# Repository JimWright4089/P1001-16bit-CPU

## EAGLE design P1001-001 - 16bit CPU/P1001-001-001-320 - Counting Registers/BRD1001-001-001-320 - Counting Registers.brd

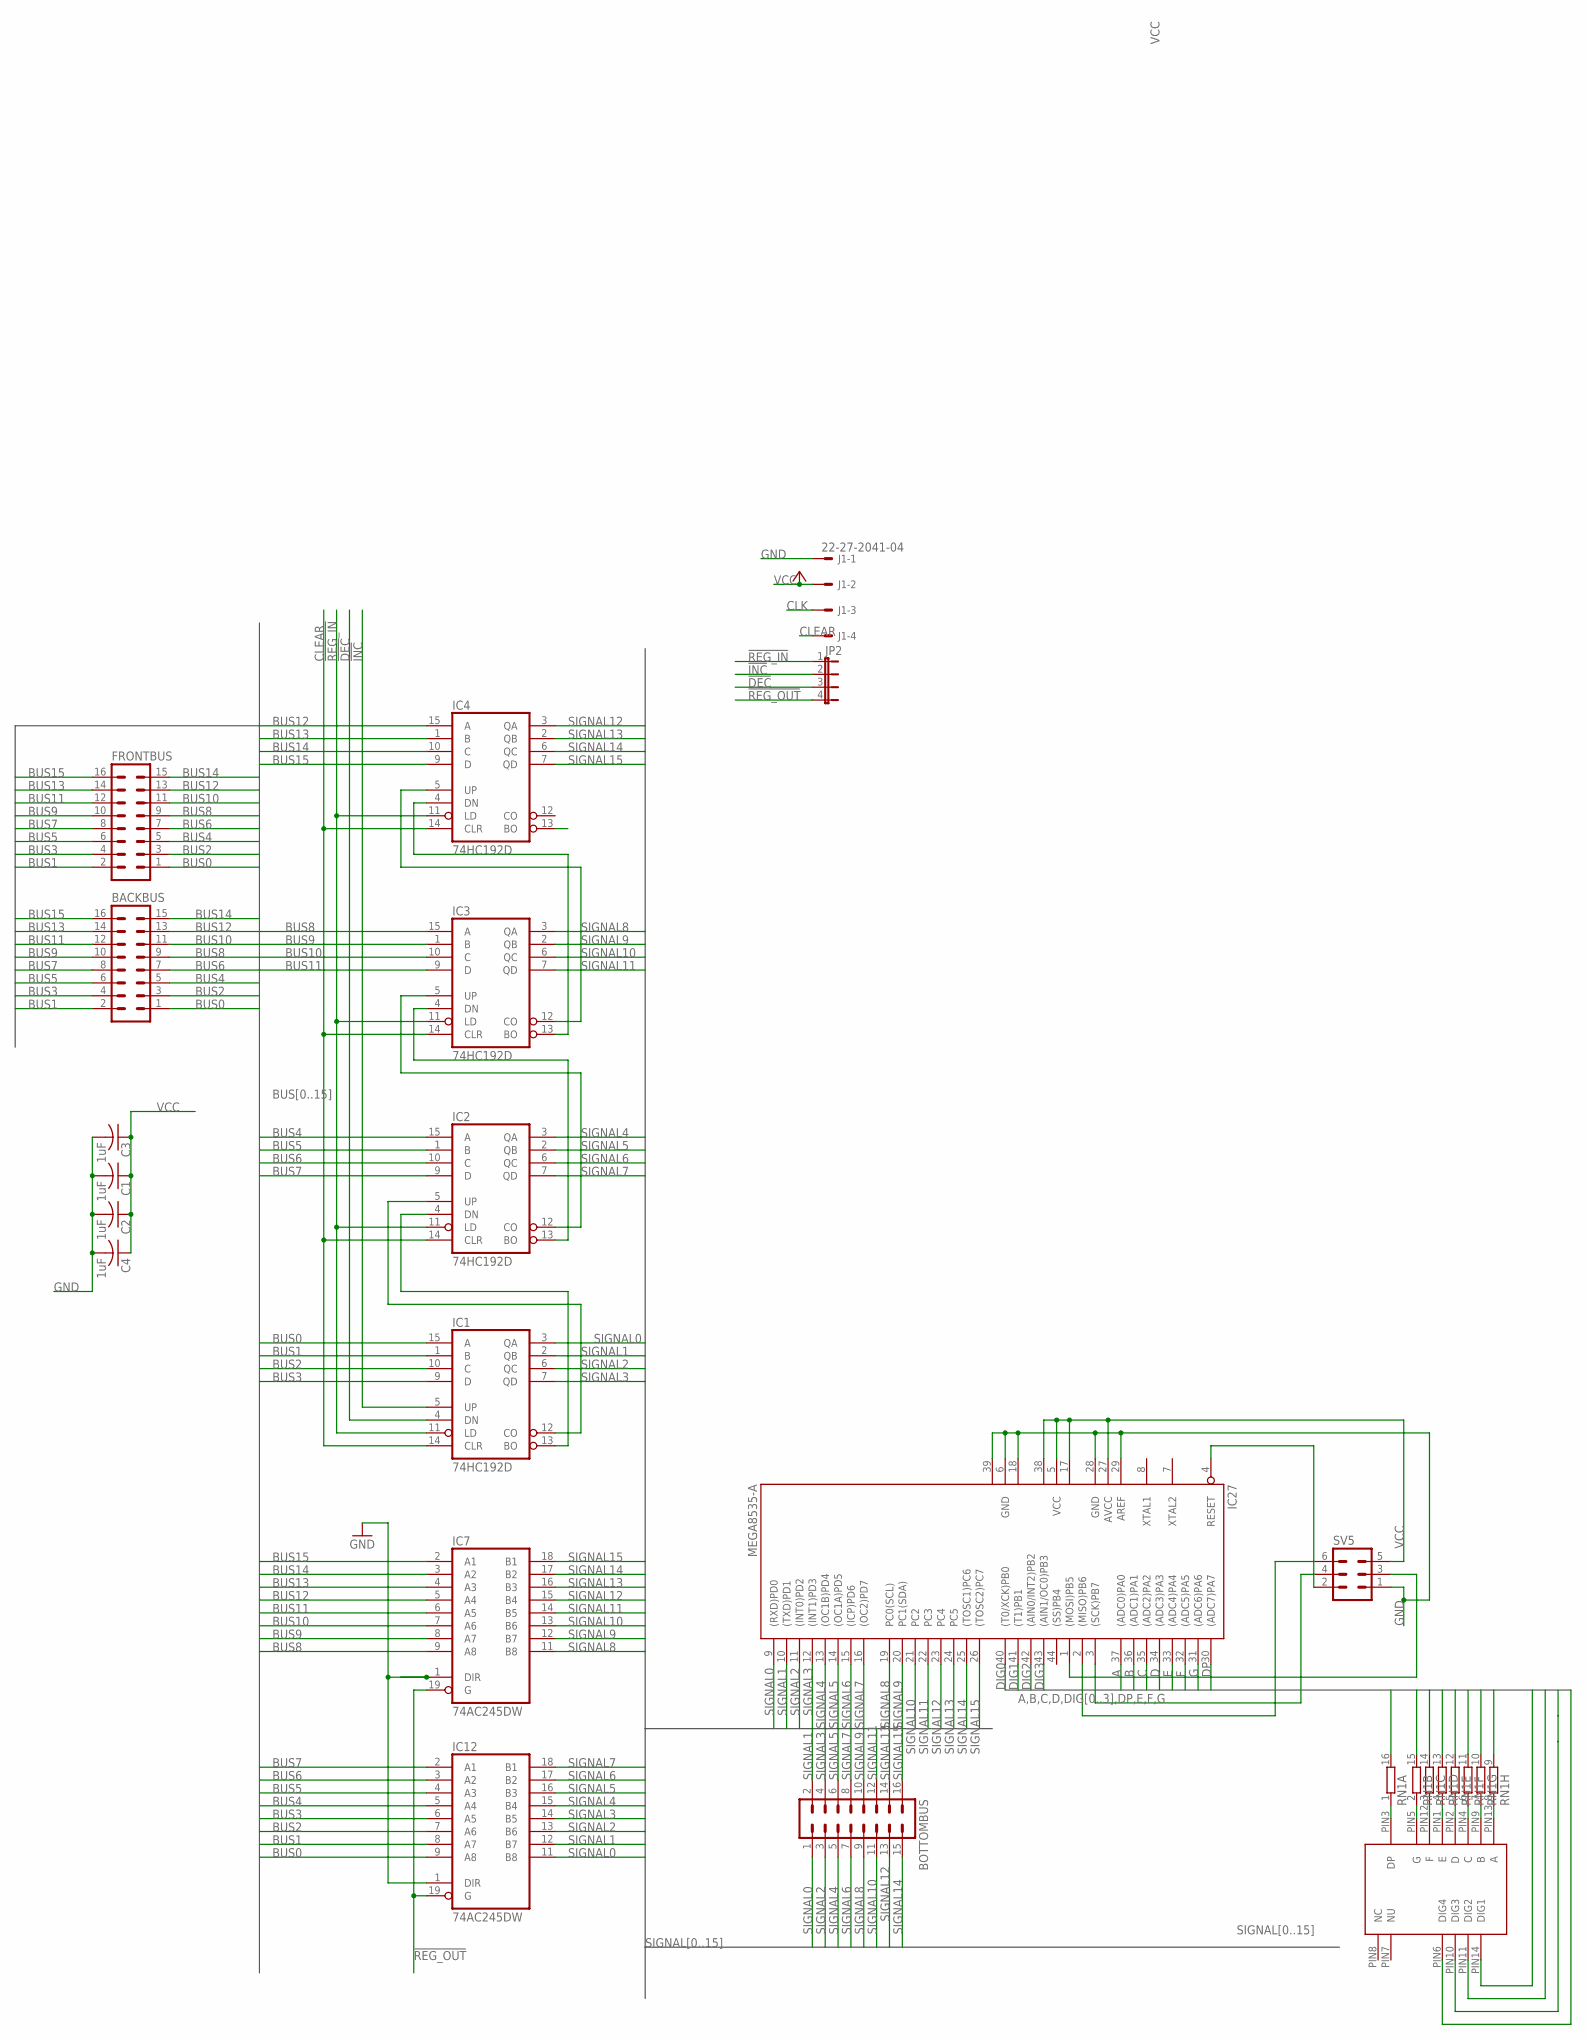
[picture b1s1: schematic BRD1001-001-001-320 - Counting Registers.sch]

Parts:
BACKBUS: ML16
BOTTOMBUS: ML16
C1, C2, C3, C4: 1uF; C1206
FRONTBUS: ML16
IC1, IC2, IC3, IC4: 74HC192D; SO16
IC7, IC12: 74AC245DW; SO20W
IC27: MEGA8535-A; TQFP44
J1: 22-27-2041-04; 6410-04
JP2: JP4E; JP4
RN1: 8R-NSOMC; SOMC16
SV5: ML6
U$1: 4-DIGIT-7-SEGMENT

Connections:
!DEC: IC1.4 (DN), JP2.3
!INC: IC1.5 (UP), JP2.2
!REG_IN: IC1.11 (LD), IC2.11 (LD), IC3.11 (LD), IC4.11 (LD), JP2.1
!REG_OUT: IC7.19 (G), IC12.19 (G), JP2.4
A: IC27.37 ((ADC0)PA0), RN1.9 (2)
B: IC27.36 ((ADC1)PA1), RN1.10 (2)
BUS0: BACKBUS.1, FRONTBUS.1, IC1.15 (A), IC12.9 (A8)
BUS1: BACKBUS.2, FRONTBUS.2, IC1.1 (B), IC12.8 (A7)
BUS2: BACKBUS.3, FRONTBUS.3, IC1.10 (C), IC12.7 (A6)
BUS3: BACKBUS.4, FRONTBUS.4, IC1.9 (D), IC12.6 (A5)
BUS4: BACKBUS.5, FRONTBUS.5, IC2.15 (A), IC12.5 (A4)
BUS5: BACKBUS.6, FRONTBUS.6, IC2.1 (B), IC12.4 (A3)
BUS6: BACKBUS.7, FRONTBUS.7, IC2.10 (C), IC12.3 (A2)
BUS7: BACKBUS.8, FRONTBUS.8, IC2.9 (D), IC12.2 (A1)
BUS8: BACKBUS.9, FRONTBUS.9, IC3.15 (A), IC7.9 (A8)
BUS9: BACKBUS.10, FRONTBUS.10, IC3.1 (B), IC7.8 (A7)
BUS10: BACKBUS.11, FRONTBUS.11, IC3.10 (C), IC7.7 (A6)
BUS11: BACKBUS.12, FRONTBUS.12, IC3.9 (D), IC7.6 (A5)
BUS12: BACKBUS.13, FRONTBUS.13, IC4.15 (A), IC7.5 (A4)
BUS13: BACKBUS.14, FRONTBUS.14, IC4.1 (B), IC7.4 (A3)
BUS14: BACKBUS.15, FRONTBUS.15, IC4.10 (C), IC7.3 (A2)
BUS15: BACKBUS.16, FRONTBUS.16, IC4.9 (D), IC7.2 (A1)
C: IC27.35 ((ADC2)PA2), RN1.11 (2)
CLEAR: IC1.14 (CLR), IC2.14 (CLR), IC3.14 (CLR), IC4.14 (CLR), J1.4
CLK: J1.3
D: IC27.34 ((ADC3)PA3), RN1.12 (2)
DIG0: IC27.40 ((T0/XCK)PB0), U$1.PIN14 (DIG1)
DIG1: IC27.41 ((T1)PB1), U$1.PIN11 (DIG2)
DIG2: IC27.42 ((AIN0/INT2)PB2), U$1.PIN10 (DIG3)
DIG3: IC27.43 ((AIN1/OC0)PB3), U$1.PIN6 (DIG4)
DP: IC27.30 ((ADC7)PA7), RN1.16 (2)
E: IC27.33 ((ADC4)PA4), RN1.13 (2)
F: IC27.32 ((ADC5)PA5), RN1.14 (2)
G: IC27.31 ((ADC6)PA6), RN1.15 (2)
GND: C1.2, C2.2, C3.2, C4.2, IC1.8 (GND), IC2.8 (GND), IC3.8 (GND), IC4.8 (GND), IC7.1 (DIR), IC7.10 (GND), IC12.1 (DIR), IC12.10 (GND), IC27.6 (GND), IC27.18 (GND1), IC27.28 (GND), IC27.29 (AREF), IC27.39 (GND2), J1.1, SV5.1
unnamed: IC1.12 (CO), IC2.5 (UP)
unnamed: IC1.13 (BO), IC2.4 (DN)
unnamed: IC2.12 (CO), IC3.5 (UP)
unnamed: IC2.13 (BO), IC3.4 (DN)
unnamed: IC3.12 (CO), IC4.5 (UP)
unnamed: IC3.13 (BO), IC4.4 (DN)
unnamed: IC27.1 ((MOSI)PB5), SV5.3
unnamed: IC27.3 ((SCK)PB7), SV5.4
unnamed: IC27.2 ((MISO)PB6), SV5.6
unnamed: IC27.4 (RESET), SV5.2
unnamed: RN1.8 (1), U$1.PIN13 (A)
unnamed: RN1.7 (1), U$1.PIN9 (B)
unnamed: RN1.6 (1), U$1.PIN4 (C)
unnamed: RN1.5 (1), U$1.PIN2 (D)
unnamed: RN1.4 (1), U$1.PIN1 (E)
unnamed: RN1.3 (1), U$1.PIN12 (F)
unnamed: RN1.2 (1), U$1.PIN5 (G)
unnamed: RN1.1, U$1.PIN3 (DP)
SIGNAL0: BOTTOMBUS.1, IC1.3 (QA), IC12.11 (B8), IC27.9 ((RXD)PD0)
SIGNAL1: BOTTOMBUS.2, IC1.2 (QB), IC12.12 (B7), IC27.10 ((TXD)PD1)
SIGNAL2: BOTTOMBUS.3, IC1.6 (QC), IC12.13 (B6), IC27.11 ((INT0)PD2)
SIGNAL3: BOTTOMBUS.4, IC1.7 (QD), IC12.14 (B5), IC27.12 ((INT1)PD3)
SIGNAL4: BOTTOMBUS.5, IC2.3 (QA), IC12.15 (B4), IC27.13 ((OC1B)PD4)
SIGNAL5: BOTTOMBUS.6, IC2.2 (QB), IC12.16 (B3), IC27.14 ((OC1A)PD5)
SIGNAL6: BOTTOMBUS.7, IC2.6 (QC), IC12.17 (B2), IC27.15 ((ICP)PD6)
SIGNAL7: BOTTOMBUS.8, IC2.7 (QD), IC12.18 (B1), IC27.16 ((OC2)PD7)
SIGNAL8: BOTTOMBUS.9, IC3.3 (QA), IC7.11 (B8), IC27.19 (PC0(SCL))
SIGNAL9: BOTTOMBUS.10, IC3.2 (QB), IC7.12 (B7), IC27.20 (PC1(SDA))
SIGNAL10: BOTTOMBUS.11, IC3.6 (QC), IC7.13 (B6), IC27.21 (PC2)
SIGNAL11: BOTTOMBUS.12, IC3.7 (QD), IC7.14 (B5), IC27.22 (PC3)
SIGNAL12: BOTTOMBUS.13, IC4.3 (QA), IC7.15 (B4), IC27.23 (PC4)
SIGNAL13: BOTTOMBUS.14, IC4.2 (QB), IC7.16 (B3), IC27.24 (PC5)
SIGNAL14: BOTTOMBUS.15, IC4.6 (QC), IC7.17 (B2), IC27.25 ((TOSC1)PC6)
SIGNAL15: BOTTOMBUS.16, IC4.7 (QD), IC7.18 (B1), IC27.26 ((TOSC2)PC7)
VCC: C1.1, C2.1, C3.1, C4.1, IC1.16 (VCC), IC2.16 (VCC), IC3.16 (VCC), IC4.16 (VCC), IC7.20 (VCC), IC12.20 (VCC), IC27.5 (VCC), IC27.17 (VCC1), IC27.27 (AVCC), IC27.38 (VCC2), J1.2, SV5.5

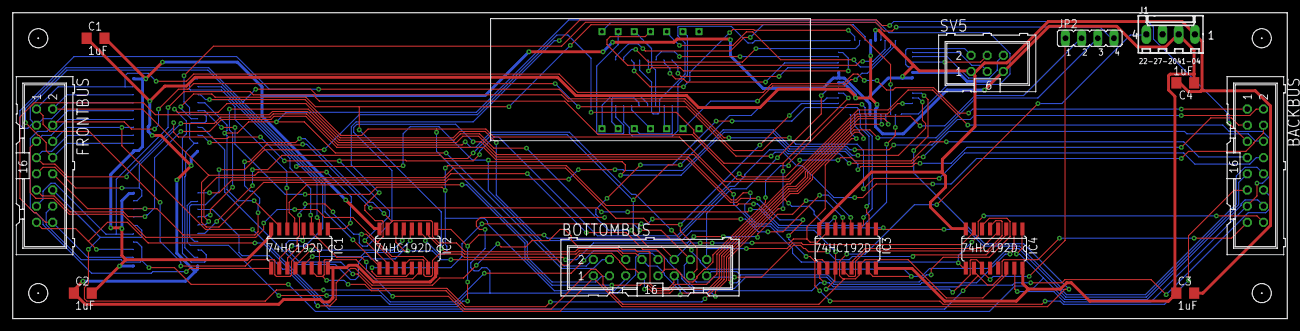
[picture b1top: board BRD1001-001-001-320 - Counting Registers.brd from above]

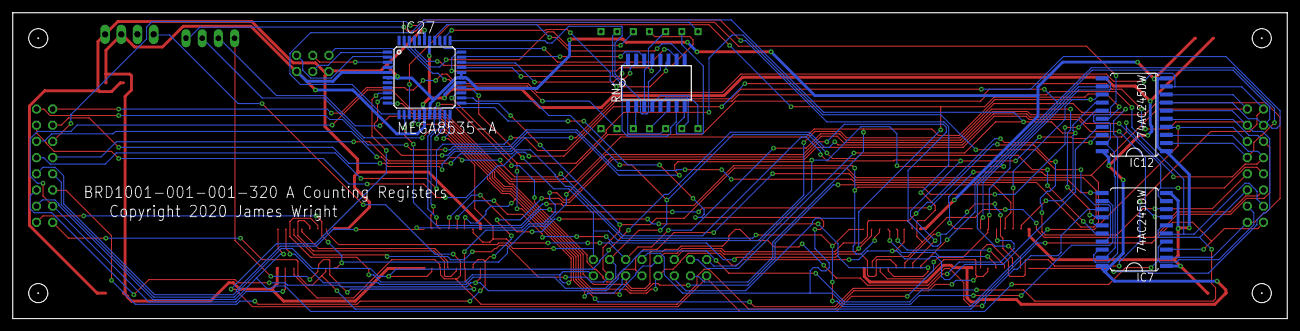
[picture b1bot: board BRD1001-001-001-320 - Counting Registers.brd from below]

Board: 2 copper layers, 200.0 x 48.0 mm, 19 parts (4 on the bottom side), 69 nets.

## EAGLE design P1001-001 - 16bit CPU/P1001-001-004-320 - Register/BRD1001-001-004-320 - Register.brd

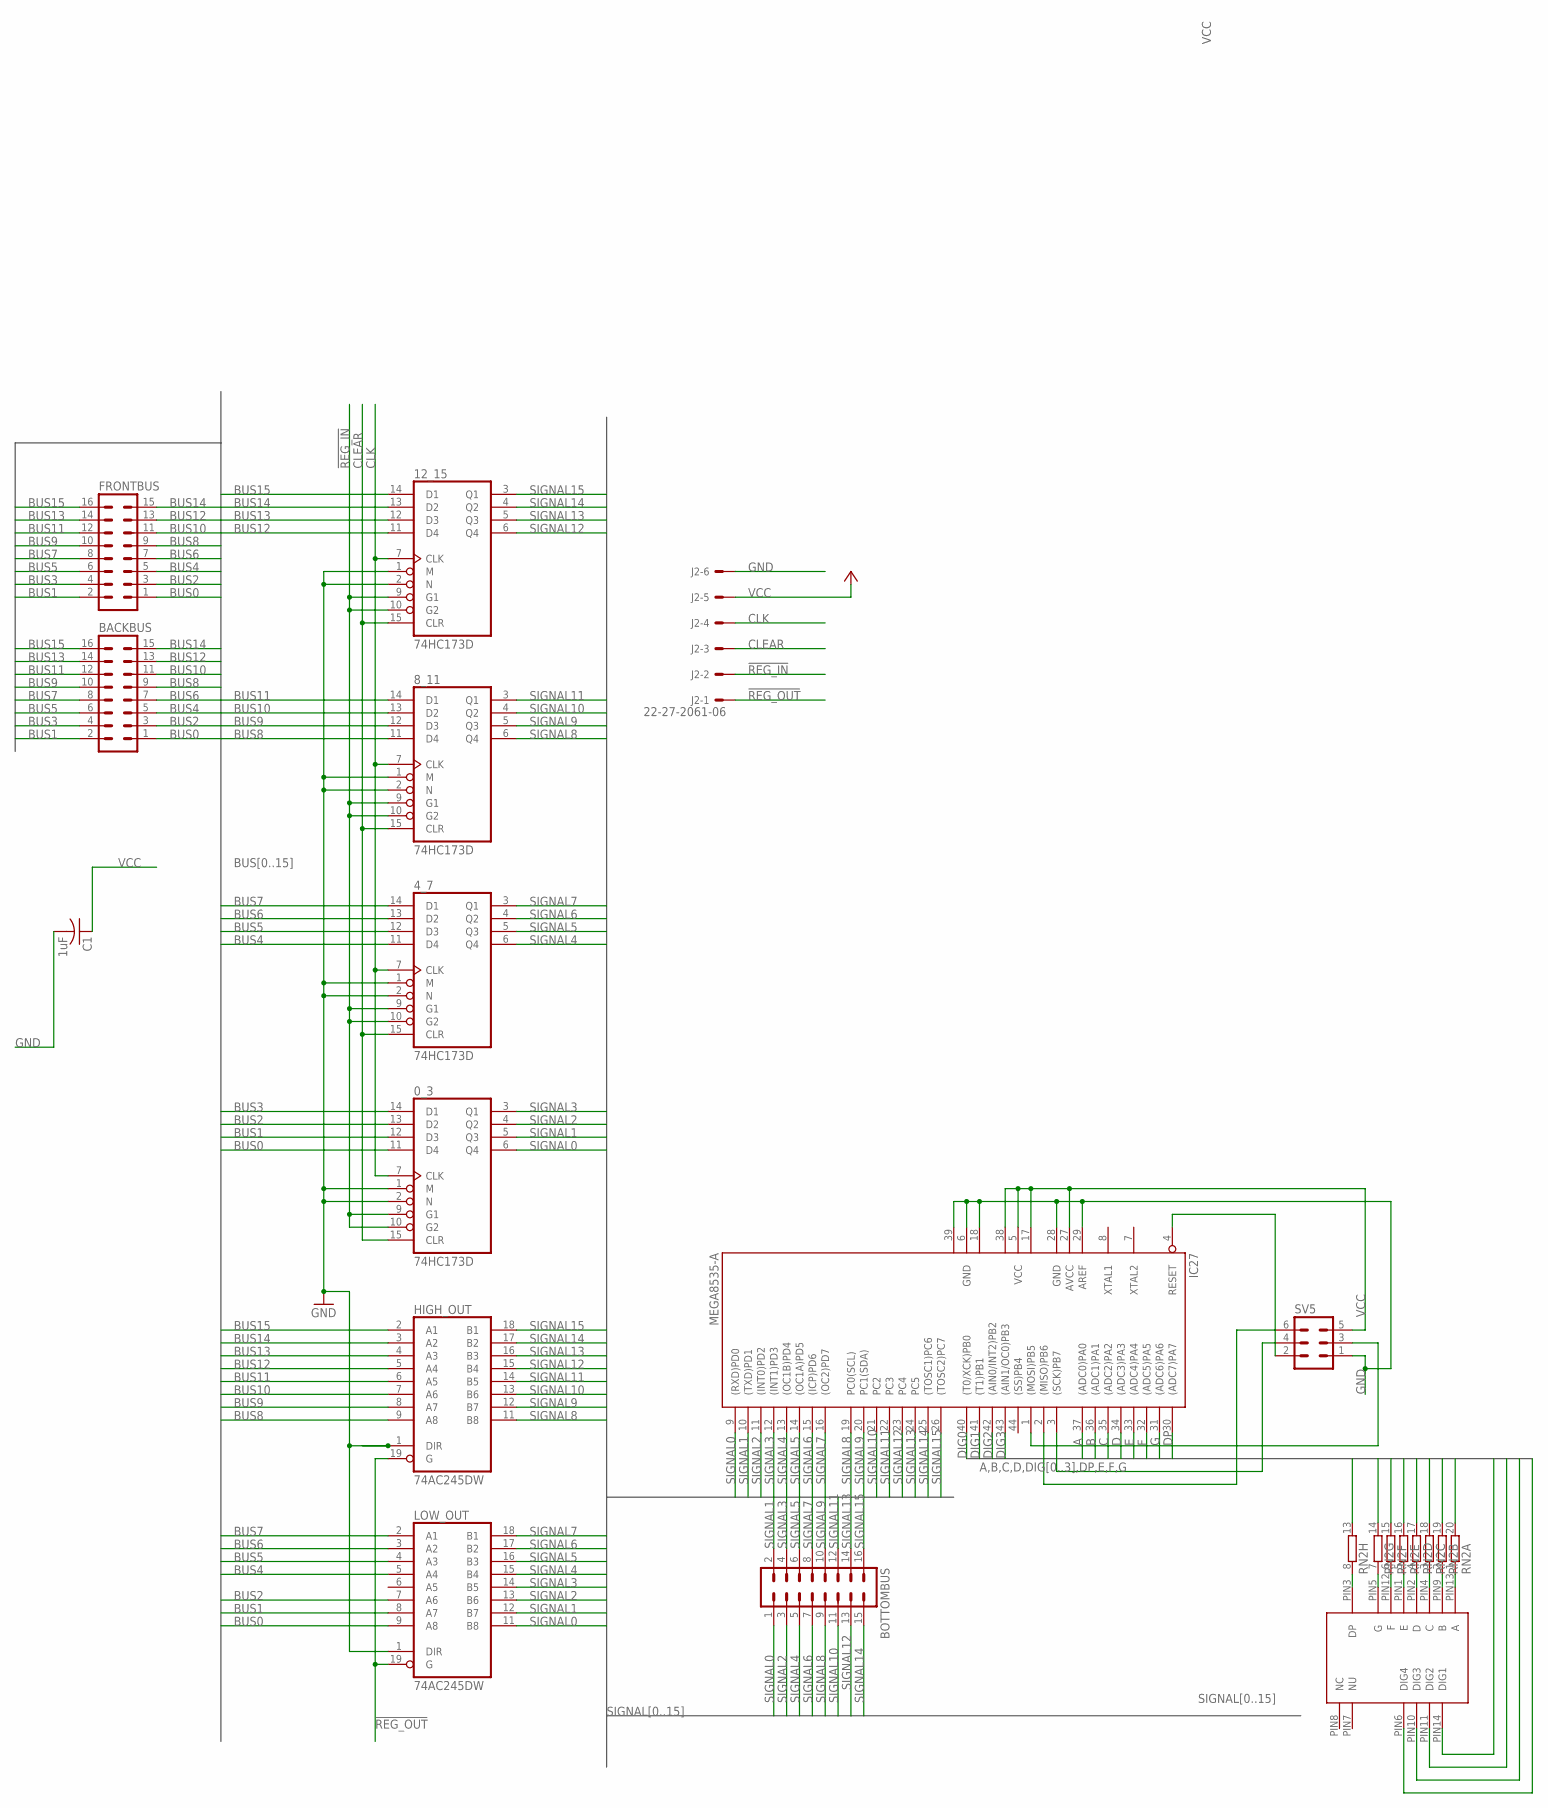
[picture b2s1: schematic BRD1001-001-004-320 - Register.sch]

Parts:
0_3, 4_7, 8_11, 12_15: 74HC173D; SO16
BACKBUS: ML16
BOTTOMBUS: ML16
C1: 1uF; C1206
FRONTBUS: ML16
HIGH_OUT: 74AC245DW; SO20W
IC27: MEGA8535-A; TQFP44
J2: 22-27-2061-06; 6410-06
LOW_OUT: 74AC245DW; SO20W
RN2: 10R-NSOMC; SOMC20
SV5: ML6
U$1: 4-DIGIT-7-SEGMENT

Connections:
!REG_IN: 0_3.9 (G1), 0_3.10 (G2), 4_7.9 (G1), 4_7.10 (G2), 8_11.9 (G1), 8_11.10 (G2), 12_15.9 (G1), 12_15.10 (G2), J2.2
!REG_OUT: HIGH_OUT.19 (G), J2.1, LOW_OUT.19 (G)
A: IC27.37 ((ADC0)PA0), RN2.20 (2)
B: IC27.36 ((ADC1)PA1), RN2.19 (2)
BUS0: 0_3.11 (D4), BACKBUS.1, FRONTBUS.1, LOW_OUT.9 (A8)
BUS1: 0_3.12 (D3), BACKBUS.2, FRONTBUS.2, LOW_OUT.8 (A7)
BUS2: 0_3.13 (D2), BACKBUS.3, FRONTBUS.3, LOW_OUT.7 (A6)
BUS3: 0_3.14 (D1), BACKBUS.4, FRONTBUS.4
BUS4: 4_7.11 (D4), BACKBUS.5, FRONTBUS.5, LOW_OUT.5 (A4)
BUS5: 4_7.12 (D3), BACKBUS.6, FRONTBUS.6, LOW_OUT.4 (A3)
BUS6: 4_7.13 (D2), BACKBUS.7, FRONTBUS.7, LOW_OUT.3 (A2)
BUS7: 4_7.14 (D1), BACKBUS.8, FRONTBUS.8, LOW_OUT.2 (A1)
BUS8: 8_11.11 (D4), BACKBUS.9, FRONTBUS.9, HIGH_OUT.9 (A8)
BUS9: 8_11.12 (D3), BACKBUS.10, FRONTBUS.10, HIGH_OUT.8 (A7)
BUS10: 8_11.13 (D2), BACKBUS.11, FRONTBUS.11, HIGH_OUT.7 (A6)
BUS11: 8_11.14 (D1), BACKBUS.12, FRONTBUS.12, HIGH_OUT.6 (A5)
BUS12: 12_15.11 (D4), BACKBUS.13, FRONTBUS.13, HIGH_OUT.5 (A4)
BUS13: 12_15.12 (D3), BACKBUS.14, FRONTBUS.14, HIGH_OUT.4 (A3)
BUS14: 12_15.13 (D2), BACKBUS.15, FRONTBUS.15, HIGH_OUT.3 (A2)
BUS15: 12_15.14 (D1), BACKBUS.16, FRONTBUS.16, HIGH_OUT.2 (A1)
C: IC27.35 ((ADC2)PA2), RN2.18 (2)
CLEAR: 0_3.15 (CLR), 4_7.15 (CLR), 8_11.15 (CLR), 12_15.15 (CLR), J2.3
CLK: 0_3.7 (CLK), 4_7.7 (CLK), 8_11.7 (CLK), 12_15.7 (CLK), J2.4
D: IC27.34 ((ADC3)PA3), RN2.17 (2)
DIG0: IC27.40 ((T0/XCK)PB0), U$1.PIN14 (DIG1)
DIG1: IC27.41 ((T1)PB1), U$1.PIN11 (DIG2)
DIG2: IC27.42 ((AIN0/INT2)PB2), U$1.PIN10 (DIG3)
DIG3: IC27.43 ((AIN1/OC0)PB3), U$1.PIN6 (DIG4)
DP: IC27.30 ((ADC7)PA7), RN2.13 (2)
E: IC27.33 ((ADC4)PA4), RN2.16 (2)
F: IC27.32 ((ADC5)PA5), RN2.15 (2)
G: IC27.31 ((ADC6)PA6), RN2.14 (2)
GND: 0_3.1 (M), 0_3.2 (N), 0_3.8 (GND), 4_7.1 (M), 4_7.2 (N), 4_7.8 (GND), 8_11.1 (M), 8_11.2 (N), 8_11.8 (GND), 12_15.1 (M), 12_15.2 (N), 12_15.8 (GND), C1.2, HIGH_OUT.1 (DIR), HIGH_OUT.10 (GND), IC27.6 (GND), IC27.18 (GND1), IC27.28 (GND), IC27.29 (AREF), IC27.39 (GND2), J2.6, LOW_OUT.1 (DIR), LOW_OUT.10 (GND), SV5.1
unnamed: IC27.1 ((MOSI)PB5), SV5.3
unnamed: IC27.3 ((SCK)PB7), SV5.4
unnamed: IC27.2 ((MISO)PB6), SV5.6
unnamed: IC27.4 (RESET), SV5.2
unnamed: RN2.1, U$1.PIN13 (A)
unnamed: RN2.2 (1), U$1.PIN9 (B)
unnamed: RN2.3 (1), U$1.PIN4 (C)
unnamed: RN2.4 (1), U$1.PIN2 (D)
unnamed: RN2.5 (1), U$1.PIN1 (E)
unnamed: RN2.6 (1), U$1.PIN12 (F)
unnamed: RN2.7 (1), U$1.PIN5 (G)
unnamed: RN2.8 (1), U$1.PIN3 (DP)
SIGNAL0: 0_3.6 (Q4), BOTTOMBUS.1, IC27.9 ((RXD)PD0), LOW_OUT.11 (B8)
SIGNAL1: 0_3.5 (Q3), BOTTOMBUS.2, IC27.10 ((TXD)PD1), LOW_OUT.12 (B7)
SIGNAL2: 0_3.4 (Q2), BOTTOMBUS.3, IC27.11 ((INT0)PD2), LOW_OUT.13 (B6)
SIGNAL3: 0_3.3 (Q1), BOTTOMBUS.4, IC27.12 ((INT1)PD3), LOW_OUT.14 (B5)
SIGNAL4: 4_7.6 (Q4), BOTTOMBUS.5, IC27.13 ((OC1B)PD4), LOW_OUT.15 (B4)
SIGNAL5: 4_7.5 (Q3), BOTTOMBUS.6, IC27.14 ((OC1A)PD5), LOW_OUT.16 (B3)
SIGNAL6: 4_7.4 (Q2), BOTTOMBUS.7, IC27.15 ((ICP)PD6), LOW_OUT.17 (B2)
SIGNAL7: 4_7.3 (Q1), BOTTOMBUS.8, IC27.16 ((OC2)PD7), LOW_OUT.18 (B1)
SIGNAL8: 8_11.6 (Q4), BOTTOMBUS.9, HIGH_OUT.11 (B8), IC27.19 (PC0(SCL))
SIGNAL9: 8_11.5 (Q3), BOTTOMBUS.10, HIGH_OUT.12 (B7), IC27.20 (PC1(SDA))
SIGNAL10: 8_11.4 (Q2), BOTTOMBUS.11, HIGH_OUT.13 (B6), IC27.21 (PC2)
SIGNAL11: 8_11.3 (Q1), BOTTOMBUS.12, HIGH_OUT.14 (B5), IC27.22 (PC3)
SIGNAL12: 12_15.6 (Q4), BOTTOMBUS.13, HIGH_OUT.15 (B4), IC27.23 (PC4)
SIGNAL13: 12_15.5 (Q3), BOTTOMBUS.14, HIGH_OUT.16 (B3), IC27.24 (PC5)
SIGNAL14: 12_15.4 (Q2), BOTTOMBUS.15, HIGH_OUT.17 (B2), IC27.25 ((TOSC1)PC6)
SIGNAL15: 12_15.3 (Q1), BOTTOMBUS.16, HIGH_OUT.18 (B1), IC27.26 ((TOSC2)PC7)
VCC: 0_3.16 (VCC), 4_7.16 (VCC), 8_11.16 (VCC), 12_15.16 (VCC), C1.1, HIGH_OUT.20 (VCC), IC27.5 (VCC), IC27.17 (VCC1), IC27.27 (AVCC), IC27.38 (VCC2), J2.5, LOW_OUT.20 (VCC), SV5.5

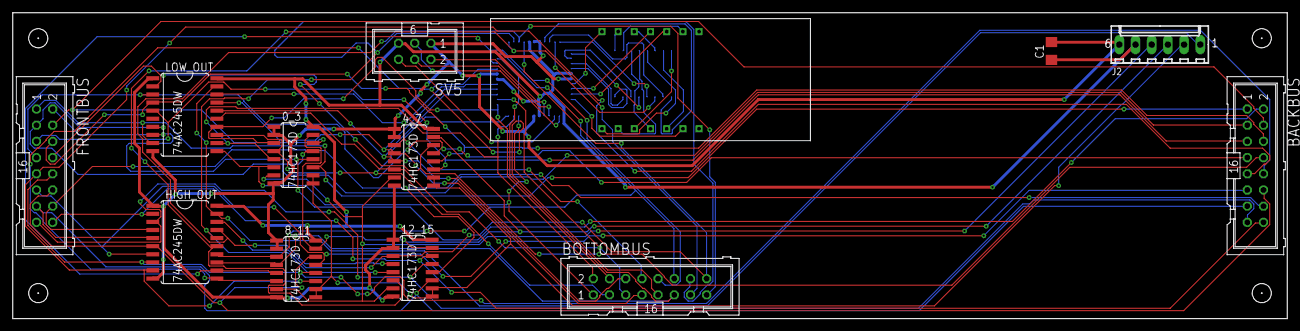
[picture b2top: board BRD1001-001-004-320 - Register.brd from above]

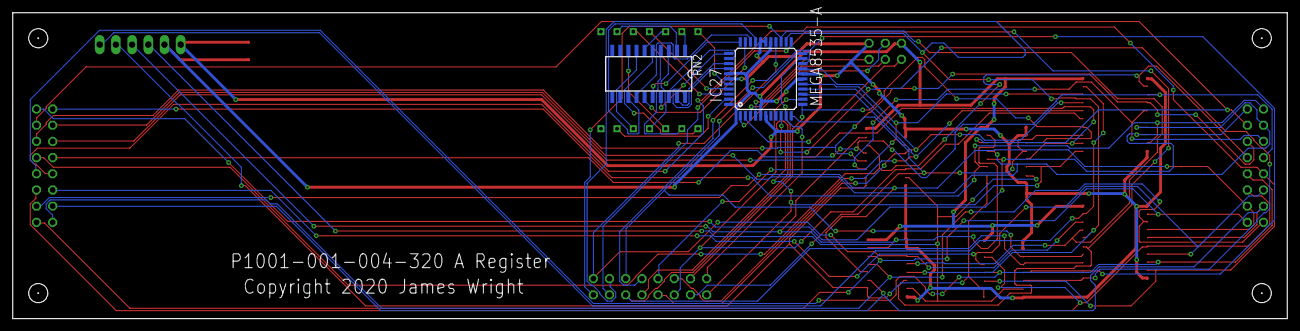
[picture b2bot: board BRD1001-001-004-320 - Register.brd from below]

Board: 2 copper layers, 200.0 x 48.0 mm, 15 parts (2 on the bottom side), 62 nets.

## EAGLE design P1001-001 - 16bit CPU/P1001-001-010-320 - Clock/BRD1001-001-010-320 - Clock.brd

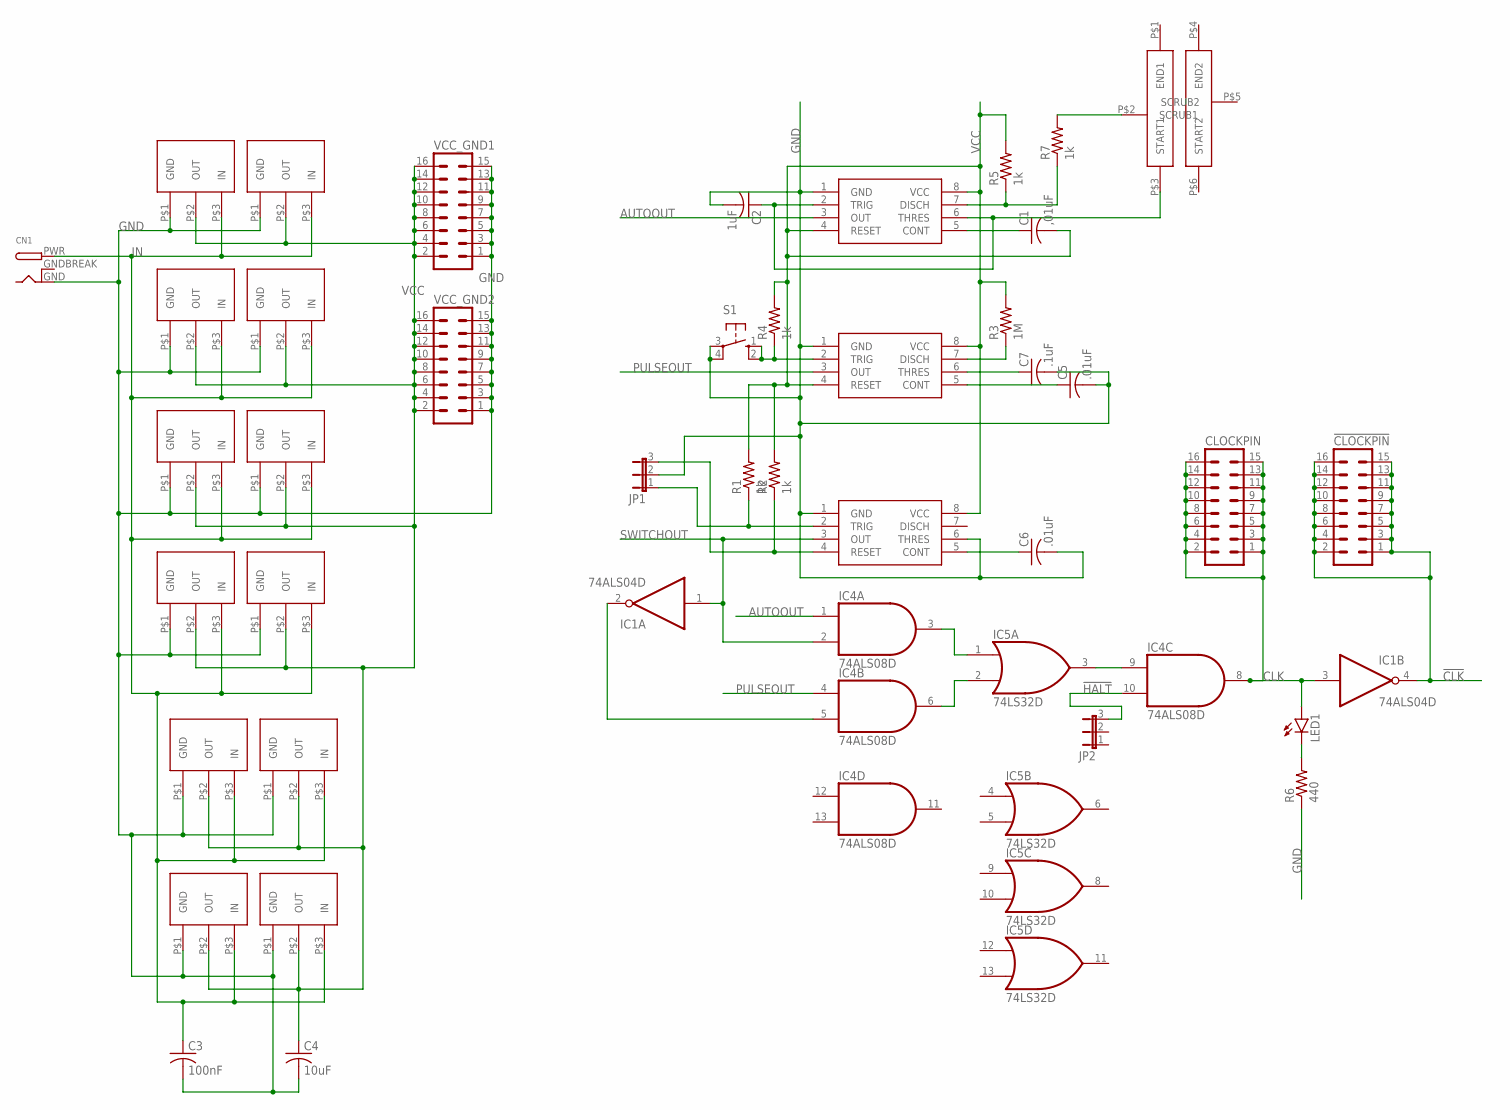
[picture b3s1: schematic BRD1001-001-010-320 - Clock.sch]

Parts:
!CLOCKPIN: ML16
AUTO: NA555; SO8
C1: ,01uF; C025-024X044
C2: 1uF; C025-024X044
C3: 100nF; C025-024X044
C4: 10uF; C025-024X044
C5, C6: .01uF; C025-024X044
C7: .1uF; C025-024X044
CLOCKPIN: ML16
CN1: DCBARRELPTH; DCJACK_2MM_PTH
IC1: 74ALS04D; SO14
IC4: 74ALS08D; SO14
IC5: 74LS32D; SO14
JP1, JP2: JP2E; JP2
LED1: LED5MM
PULSE: NA555; SO8
R1, R2, R4, R5, R7: 1k; 0204V
R3: 1M; 0204V
R6: 440; 0204V
S1: 40-XX; B3F-40XX
SWITCH: NA555; SO8
U$1: 3310H-001-105L
U$2, U$3, U$4, U$5, U$6, U$7, U$8, U$9, U$10, U$11, U$12, U$13: LD1117S33TR; AZ1117E
VCC_GND1, VCC_GND2: ML16

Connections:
!CLK: !CLOCKPIN.1, !CLOCKPIN.2, !CLOCKPIN.3, !CLOCKPIN.4, !CLOCKPIN.5, !CLOCKPIN.6, !CLOCKPIN.7, !CLOCKPIN.8, !CLOCKPIN.9, !CLOCKPIN.10, !CLOCKPIN.11, !CLOCKPIN.12, !CLOCKPIN.13, !CLOCKPIN.14, !CLOCKPIN.15, !CLOCKPIN.16, IC1.4 (O)
!HALT: IC4.10 (I1), JP2.3
AUTOOUT: AUTO.3 (OUT), IC4.1 (I0)
CLK: CLOCKPIN.1, CLOCKPIN.2, CLOCKPIN.3, CLOCKPIN.4, CLOCKPIN.5, CLOCKPIN.6, CLOCKPIN.7, CLOCKPIN.8, CLOCKPIN.9, CLOCKPIN.10, CLOCKPIN.11, CLOCKPIN.12, CLOCKPIN.13, CLOCKPIN.14, CLOCKPIN.15, CLOCKPIN.16, IC1.3 (I), IC4.8 (O), LED1.A
GND: AUTO.1 (GND), C2.2, C3.2, C4.2, C5.2, C6.2, C7.2, CN1.GND, IC1.7 (GND), IC4.7 (GND), IC5.7 (GND), JP1.2, PULSE.1 (GND), R6.1, S1.3, S1.4 (P1), SWITCH.1 (GND), SWITCH.6 (THRES), U$2.P$1 (GND), U$3.P$1 (GND), U$4.P$1 (GND), U$5.P$1 (GND), U$6.P$1 (GND), U$7.P$1 (GND), U$8.P$1 (GND), U$9.P$1 (GND), U$10.P$1 (GND), U$11.P$1 (GND), U$12.P$1 (GND), U$13.P$1 (GND), VCC_GND1.1, VCC_GND1.3, VCC_GND1.5, VCC_GND1.7, VCC_GND1.9, VCC_GND1.11, VCC_GND1.13, VCC_GND1.15, VCC_GND2.1, VCC_GND2.3, VCC_GND2.5, VCC_GND2.7, VCC_GND2.9, VCC_GND2.11, VCC_GND2.13, VCC_GND2.15
GNDBREAK: CN1.GNDBREAK
IN: C3.1, CN1.PWR, U$2.P$3 (IN), U$3.P$3 (IN), U$4.P$3 (IN), U$5.P$3 (IN), U$6.P$3 (IN), U$7.P$3 (IN), U$8.P$3 (IN), U$9.P$3 (IN), U$10.P$3 (IN), U$11.P$3 (IN), U$12.P$3 (IN), U$13.P$3 (IN)
unnamed: AUTO.2 (TRIG), AUTO.6 (THRES), C2.1, U$1.P$3 (START1)
unnamed: LED1.K (C), R6.2
unnamed: AUTO.5 (CONT), C1.1
unnamed: R7.2, U$1.P$2 (SCRUB1)
unnamed: AUTO.7 (DISCH), R5.1, R7.1
unnamed: PULSE.2 (TRIG), R4.1, S1.1 (S), S1.2 (S1)
unnamed: C7.1, PULSE.6 (THRES)
unnamed: C5.1, PULSE.5 (CONT)
unnamed: PULSE.7 (DISCH), R3.1
unnamed: C6.1, SWITCH.5 (CONT)
unnamed: JP1.3, R2.1, SWITCH.4 (RESET)
unnamed: JP1.1, R1.1, SWITCH.2 (TRIG)
unnamed: IC1.2 (O), IC4.5 (I1)
unnamed: IC4.3 (O), IC5.1 (I0)
unnamed: IC4.6 (O), IC5.2 (I1)
unnamed: IC4.9 (I0), IC5.3 (O)
PULSEOUT: IC4.4 (I0), PULSE.3 (OUT)
SWITCHOUT: IC1.1 (I), IC4.2 (I1), SWITCH.3 (OUT)
VCC: AUTO.4 (RESET), AUTO.8 (VCC), C1.2, C4.1, IC1.14 (VCC), IC4.14 (VCC), IC5.14 (VCC), PULSE.4 (RESET), PULSE.8 (VCC), R1.2, R2.2, R3.2, R4.2, R5.2, SWITCH.8 (VCC), U$2.P$2 (OUT), U$3.P$2 (OUT), U$4.P$2 (OUT), U$5.P$2 (OUT), U$6.P$2 (OUT), U$7.P$2 (OUT), U$8.P$2 (OUT), U$9.P$2 (OUT), U$10.P$2 (OUT), U$11.P$2 (OUT), U$12.P$2 (OUT), U$13.P$2 (OUT), VCC_GND1.2, VCC_GND1.4, VCC_GND1.6, VCC_GND1.8, VCC_GND1.10, VCC_GND1.12, VCC_GND1.14, VCC_GND1.16, VCC_GND2.2, VCC_GND2.4, VCC_GND2.6, VCC_GND2.8, VCC_GND2.10, VCC_GND2.12, VCC_GND2.14, VCC_GND2.16

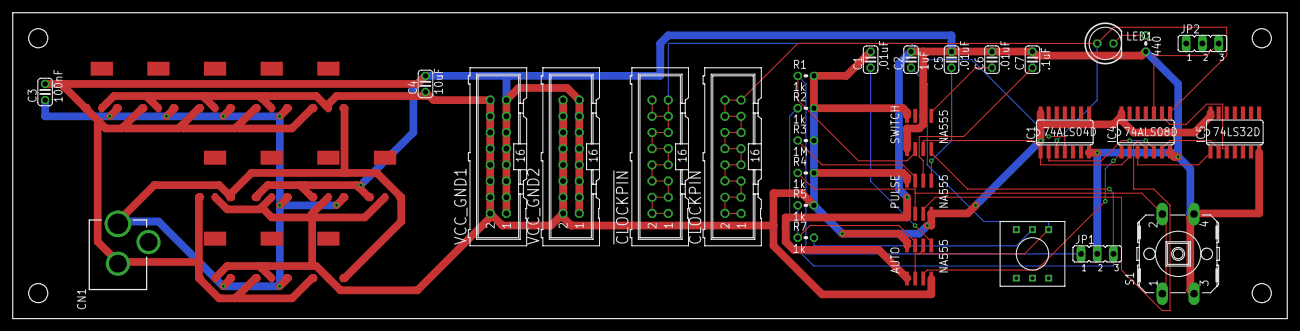
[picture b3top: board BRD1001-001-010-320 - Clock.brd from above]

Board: 2 copper layers, 200.0 x 48.0 mm, 42 parts (0 on the bottom side), 25 nets.

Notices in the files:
P1001-001 - 16bit CPU/P1001-001-001-320 - Counting Registers/BRD1001-001-001-320 - Counting Registers.brd:
Copyright 2020 James Wright
